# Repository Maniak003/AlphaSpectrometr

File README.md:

<!DOCTYPE html>
<html lang="en" data-color-mode="auto" data-light-theme="light" data-dark-theme="dark">
  <head>
    <meta charset="utf-8">
  </head>
    <body class="logged-in env-production page-responsive page-blob" style="word-wrap: break-word;">
      <p> Alpha spectrometr.<br><b></p>
      
    </body>
</html>

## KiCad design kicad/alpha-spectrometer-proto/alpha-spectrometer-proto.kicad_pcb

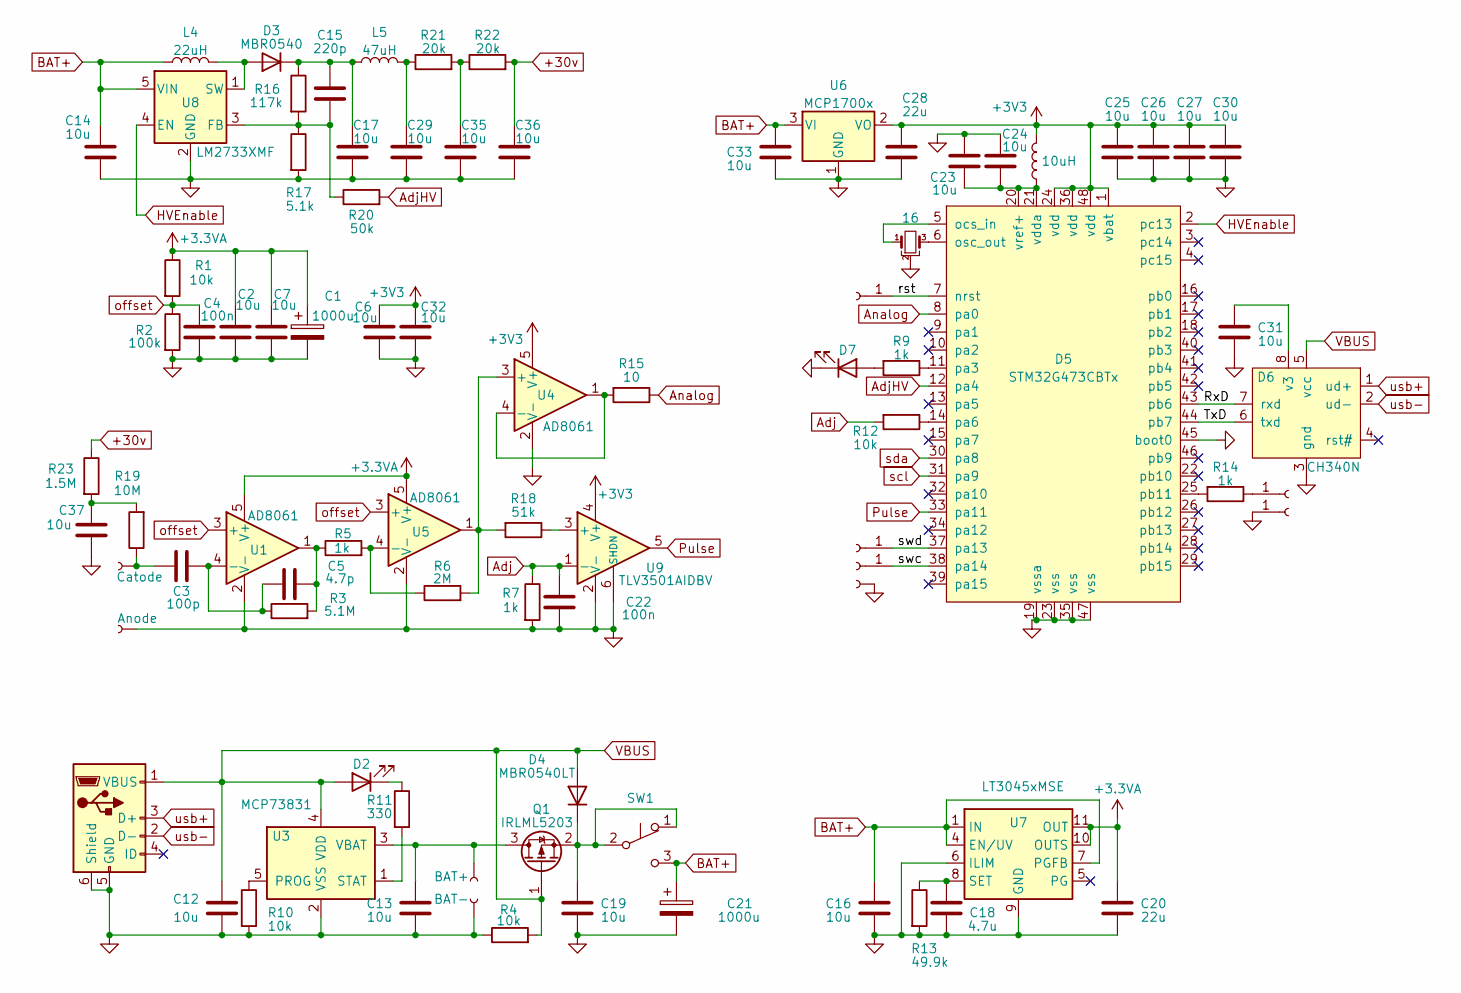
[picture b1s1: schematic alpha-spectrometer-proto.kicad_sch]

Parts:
C1, C21: 1000u; CP_EIA-7132-28_AVX-C
C2, C6, C7, C16, C23, C24, C25, C26, C27, C30, C31, C32, C33, C37: 10u; C_0603_1608Metric
C3: 100p; C_0603_1608Metric
C4, C22: 100n; C_0603_1608Metric
C5: 4.7p; C_0603_1608Metric
C12, C13, C14, C17, C19, C29, C35, C36: 10u; C_0805_2012Metric
C15: 220p; C_0603_1608Metric
C18: 4.7u; C_0603_1608Metric
C20, C28: 22u; C_0603_1608Metric
D2, D7: LED; LED_0603_1608Metric
D3: MBR0540; D_SOD-123
D4: MBR0540LT; D_SOD-123
D5: STM32G473CBTx; LQFP-48_7x7mm_P0.5mm
D6: CH340N; SOP-8_3.9x4.9mm_P1.27mm
J1: USB_B_Micro; USB_Micro-B_Amphenol_10104110_Horizontal
J2, J3, J20, J21, J22: Conn_01x01_Female; conn_mini
J4: BAT+; SMD-CONN
J5: BAT-; SMD-CONN
J13: Anode; Pin_D0.7mm_L6.5mm_W1.8mm_FlatFork
J14: Catode; Pin_D0.7mm_L6.5mm_W1.8mm_FlatFork
J19: Conn; SMD-CONN
L3: 10uH; L_0805_2012Metric
L4: 22uH; L_1206_3216Metric_Pad1.42x1.75mm_HandSolder
L5: 47uH; L_0805_2012Metric
Q1: IRLML5203; SOT-23
R1, R4, R10, R12: 10k; R_0603_1608Metric
R2: 100k; R_0603_1608Metric
R3: 5.1M; R_0603_1608Metric
R5, R7, R9, R14: 1k; R_0603_1608Metric
R6: 2M; R_0603_1608Metric
R11: 330; R_0603_1608Metric
R13: 49.9k; R_0603_1608Metric
R15: 10; R_0603_1608Metric
R16: 117k; R_0603_1608Metric
R17: 5.1k; R_0603_1608Metric
R18: 51k; R_0603_1608Metric
R19: 10M; R_0603_1608Metric
R20: 50k; R_0603_1608Metric
R21, R22: 20k; R_0603_1608Metric
R23: 1.5M; R_0603_1608Metric
SW1: SW_Push_SPDT; MySwithc
U1, U4, U5: AD8061; TSOT-23-5
U3: MCP73831; SOT-23-5
U6: MCP1700x; SOT-23
U7: LT3045xMSE; MSOP-12-1EP_3x4mm_P0.65mm_EP1.65x2.85mm
U8: LM2733XMF; SOT-23-5
U9: TLV3501AIDBV; SOT-23-6
Y1: 16; Resonator_SMD_Murata_CSTxExxV-3Pin_3.0x1.1mm

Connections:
+3.3VA: C1.1, C2.2, C7.2, C20.2, R1.1, U1.5 (V+), U5.5 (V+), U7.10 (OUTS), U7.11 (OUT), U7.12 (OUT)
+3V3: C6.2, C25.2, C26.2, C27.2, C28.2, C30.2, C32.2, D5.1 (vbat), D5.24 (vdd), D5.36 (vdd), D5.48 (vdd), L3.2, U4.5 (V+), U6.2 (VO), U9.4 (V+)
+30v: C36.2, R22.2, R23.1
/RxD: D5.43 (pb6), D6.7 (rxd)
/TxD: D5.44 (pb7), D6.6 (txd)
/rst: D5.7 (nrst), J20.1
/swc: D5.38 (pa14), J22.1
/swd: D5.37 (pa13), J21.1
Adj: C22.2, R7.1, R12.2, U9.1 (-)
AdjHV: D5.12 (pa4), R20.2
Analog: D5.8 (pa0), R15.1
BAT+: C14.2, C16.2, C21.1, C33.2, L4.1, SW1.3 (C), U6.3 (VI), U7.1 (IN), U7.2 (IN), U7.3 (IN), U7.4 (EN/UV), U7.7 (PGFB), U8.5 (VIN)
GND: C1.2, C2.1, C4.1, C6.1, C7.1, C12.1, C13.1, C14.1, C16.1, C17.1, C18.1, C19.1, C20.1, C21.2, C22.1, C23.2, C24.2, C25.1, C26.1, C27.1, C28.1, C29.1, C30.1, C31.1, C32.1, C33.1, C35.1, C36.1, C37.1, D5.19 (vssa), D5.23 (vss), D5.35 (vss), D5.45 (boot0), D5.47 (vss), D6.3 (gnd), D7.1 (K), J1.5 (GND), J1.6 (Shield), J3.1, J5.1, J13.1, J19.1, R2.2, R4.1, R7.2, R10.2, R13.2, R17.2, U1.2 (V-), U3.2 (VSS), U4.2 (V-), U5.2 (V-), U6.1 (GND), U7.6 (ILIM), U7.9 (GND), U7.13 (GND), U8.2 (GND), U9.2 (V-), U9.6 (SHDN), Y1.2
HVEnable: D5.2 (pc13), U8.4 (EN)
unnamed: C3.1, J14.1, R19.1
unnamed: C5.2, R3.2, R5.1, U1.1
unnamed: C29.2, L5.2, R21.1
unnamed: C35.2, R21.2, R22.1
unnamed: C37.2, R19.2, R23.2
unnamed: D2.1 (K), R11.1
unnamed: D3.2 (A), L4.2, U8.1 (SW)
unnamed: C15.2, C17.2, D3.1 (K), L5.1, R16.1
unnamed: C19.2, D4.1 (K), Q1.2 (S), SW1.1 (A), SW1.2 (B)
unnamed: D5.5 (ocs_in), Y1.1
unnamed: D5.6 (osc_out), Y1.3
unnamed: D5.11 (pa3), R9.1
unnamed: D5.14 (pa6), R12.1
unnamed: D5.25 (pb11), R14.2
unnamed: C23.1, C24.1, D5.20 (vref+), D5.21 (vdda), L3.1
unnamed: C31.2, D6.8 (v3)
unnamed: D7.2 (A), R9.2
unnamed: J2.1, R14.1
unnamed: C13.2, J4.1, Q1.3 (D), U3.3 (VBAT)
unnamed: C3.2, C5.1, R3.1, U1.4 (-)
unnamed: R10.1, U3.5 (PROG)
unnamed: R11.2, U3.1 (STAT)
unnamed: R6.2, R18.2, U4.3 (+), U5.1
unnamed: R15.2, U4.1, U4.4 (-)
unnamed: R5.2, R6.1, U5.4 (-)
unnamed: C18.2, R13.1, U7.8 (SET)
unnamed: C15.1, R16.2, R17.1, R20.1, U8.3 (FB)
unnamed: R18.1, U9.3 (+)
Pulse: D5.33 (pa11), U9.5
VBUS: C12.2, D2.2 (A), D4.2 (A), D6.5 (vcc), J1.1 (VBUS), Q1.1 (G), R4.2, U3.4 (VDD)
offset: C4.2, R1.2, R2.1, U1.3 (+), U5.3 (+)
scl: D5.31 (pa9)
sda: D5.30 (pa8)
usb+: D6.1 (ud+), J1.3 (D+)
usb-: D6.2 (ud-), J1.2 (D-)

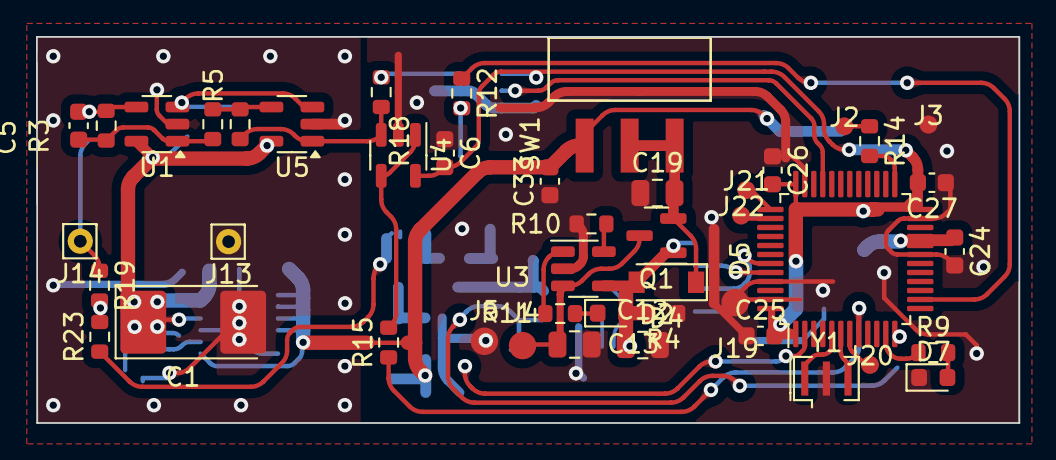
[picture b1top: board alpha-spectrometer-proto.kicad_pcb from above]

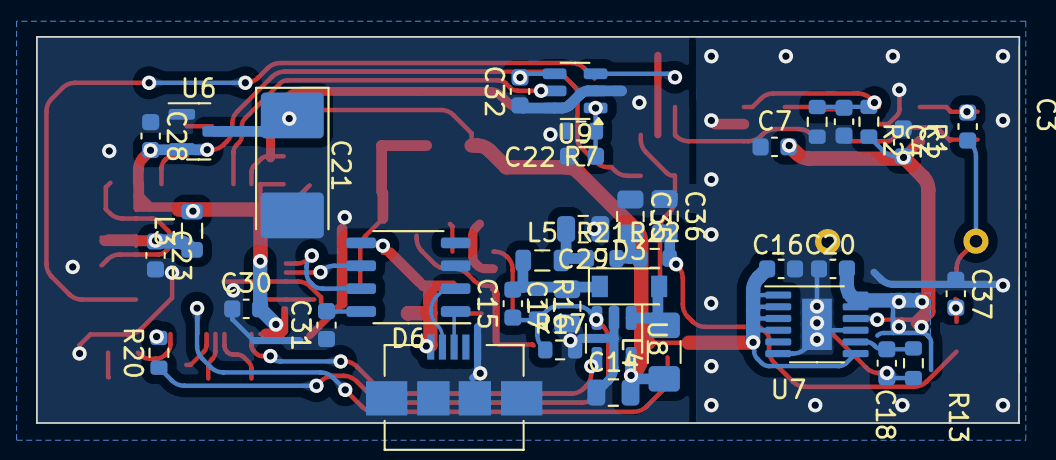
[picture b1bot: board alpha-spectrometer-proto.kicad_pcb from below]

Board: 2 copper layers, 54.6 x 21.5 mm, 85 parts (40 on the bottom side), 47 nets.

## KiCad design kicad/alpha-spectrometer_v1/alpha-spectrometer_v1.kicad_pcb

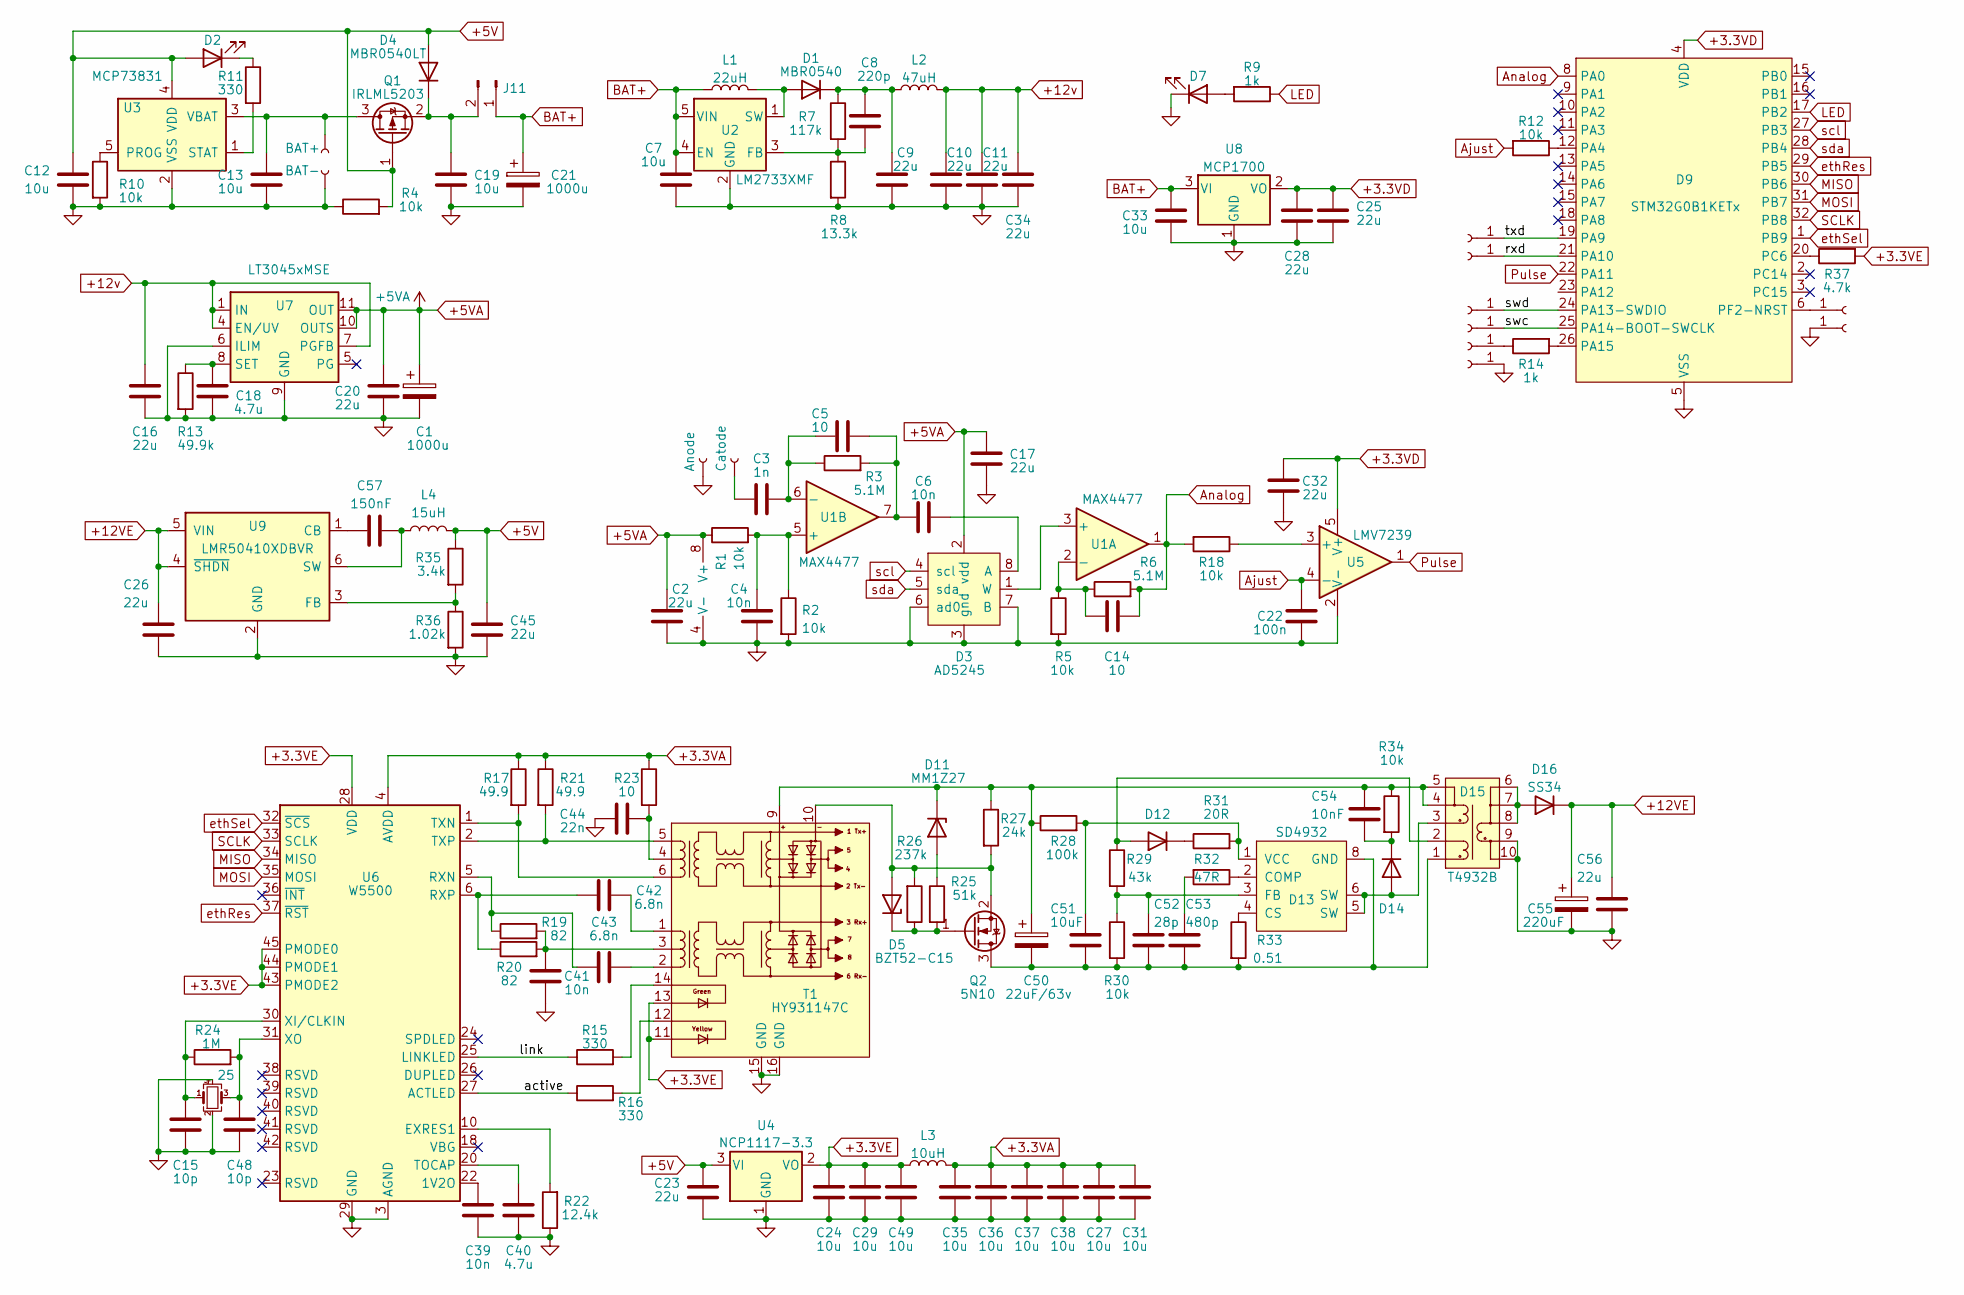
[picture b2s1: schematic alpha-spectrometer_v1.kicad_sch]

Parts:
C1: 1000u; CP_EIA-7132-20_AVX-U
C2, C16, C17, C20, C25, C28, C32: 22u; C_0603_1608Metric
C3: 1n; C_0603_1608Metric
C4, C6, C39, C41: 10n; C_0603_1608Metric
C5, C14: 10; C_0603_1608Metric
C7, C12, C13, C19: 10u; C_0805_2012Metric
C8: 220p; C_0603_1608Metric
C9, C10, C11, C23, C26, C34, C45, C56: 22u; C_0805_2012Metric
C15, C48: 10p; C_0402_1005Metric
C18, C40: 4.7u; C_0603_1608Metric
C21: 1000u; CP_EIA-7343-15_Kemet-W
C22: 100n; C_0603_1608Metric
C24, C27, C29, C31, C33, C35, C36, C37, C38: 10u; C_0603_1608Metric
C42, C43: 6.8n; C_0603_1608Metric
C44: 22n; C_0603_1608Metric
C49: 10u; C_0402_1005Metric
C50: 22uF/63v; CP_Elec_6.3x7.7
C51: 10uF; C_0805_2012Metric
C52: 28p; C_0603_1608Metric
C53: 480p; C_0603_1608Metric
C54: 10nF; C_0603_1608Metric
C55: 220uF; CP_EIA-7343-15_Kemet-W
C57: 150nF; C_0603_1608Metric
D1: MBR0540; D_SOD-123
D2, D7: LED; LED_0603_1608Metric
D3: AD5245; SOT-23-8_Handsoldering
D4: MBR0540LT; D_SOD-123
D5: BZT52-C15; D_SOD-123
D9: STM32G0B1KETx; LQFP-32_7x7mm_P0.8mm
D11: MM1Z27; D_SOD-123
D12, D14: F7; D_SOD-123
D13: SD4932; SOIC-8-N7_3.9x4.9mm_P1.27mm
D15: T4932B; DA2257
D16: SS34; D_SMB
J1, J2, J3, J6, J7, J8, J9, J10: Conn_01x01_Female; conn_mini
J4: BAT+; SMD-CONN
J5: BAT-; SMD-CONN
J11: Conn_01x02_Male; PinHeader_1x02_P2.54mm_Vertical
J13: Anode; Pin_D0.7mm_L6.5mm_W1.8mm_FlatFork
J14: Catode; Pin_D0.7mm_L6.5mm_W1.8mm_FlatFork
L1: 22uH; L_1206_3216Metric_Pad1.42x1.75mm_HandSolder
L2: 47uH; L_0805_2012Metric
L3: 10uH; L_0805_2012Metric
L4: 15uH; L_Abracon_ASPI-0630LR
Q1: IRLML5203; SOT-23
Q2: 5N10; SOT-23
R1, R2, R4, R5, R10, R12, R18, R30, R34: 10k; R_0603_1608Metric
R3, R6: 5.1M; R_0603_1608Metric
R7: 117k; R_0603_1608Metric
R8: 13.3k; R_0603_1608Metric
R9, R14: 1k; R_0603_1608Metric
R11, R15, R16: 330; R_0603_1608Metric
R13: 49.9k; R_0603_1608Metric
R17, R21: 49.9; R_0603_1608Metric
R19, R20: 82; R_0603_1608Metric
R22: 12.4k; R_0603_1608Metric
R23: 10; R_0603_1608Metric
R24: 1M; R_0402_1005Metric
R25: 51k; R_0603_1608Metric
R26: 237k; R_0603_1608Metric
R27: 24k; R_0603_1608Metric
R28: 100k; R_0603_1608Metric
R29: 43k; R_0603_1608Metric
R31: 20R; R_0603_1608Metric
R32: 47R; R_0603_1608Metric
R33: 0.51; R_0603_1608Metric
R35: 3.4k; R_0603_1608Metric
R36: 1.02k; R_0603_1608Metric
R37: 4.7k; R_0603_1608Metric
T1: HY931147C
U1: MAX4477; SSOP-8_2.95x2.8mm_P0.65mm
U2: LM2733XMF; SOT-23-5
U3: MCP73831; SOT-23-5
U4: NCP1117-3.3; SOT-223-3_TabPin2
U5: LMV7239; SOT-23-5
U6: W5500; LQFP-48_7x7mm_P0.5mm
U7: LT3045xMSE; MSOP-12-1EP_3x4mm_P0.65mm_EP1.65x2.85mm
U8: MCP1700; SOT-23
U9: LMR50410XDBVR; SOT-23-6
Y1: 25; Crystal_SMD_TXC_7M-4Pin_3.2x2.5mm

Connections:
+3.3VA: C27.2, C31.2, C35.2, C36.2, C37.2, C38.2, L3.2, R17.1, R21.1, R23.1, U6.4 (AVDD), U6.8 (AVDD), U6.11 (AVDD), U6.15 (AVDD), U6.17 (AVDD), U6.21 (AVDD)
+3.3VD: C25.2, C28.2, C32.2, D9.4 (VDD), U5.5 (V+), U8.2 (VO)
+3.3VE: C24.2, C29.2, C49.2, L3.1, R37.2, T1.11, T1.13, U4.2 (VO), U6.28 (VDD), U6.43 (PMODE2), U6.44 (PMODE1), U6.45 (PMODE0)
+5V: C12.2, C23.2, C45.2, D2.2 (A), D4.2 (A), L4.2, Q1.1 (G), R4.2, R35.1, U3.4 (VDD), U4.3 (VI)
+5VA: C1.1, C2.2, C17.2, C20.2, D3.2 (vdd), R1.1, U1.8 (V+), U7.10 (OUTS), U7.11 (OUT), U7.12 (OUT)
+12VE: C26.1, C55.1, C56.1, D16.1 (K), U9.4 (~SHDN), U9.5 (VIN)
+12v: C10.2, C11.2, C16.2, C34.2, L2.2, U7.1 (IN), U7.2 (IN), U7.3 (IN), U7.4 (EN/UV), U7.7 (PGFB)
/active: R16.1, U6.27 (ACTLED)
/link: R15.1, U6.25 (LINKLED)
/rxd: D9.21 (PA10), J9.1
/swc: D9.25 (PA14-BOOT-SWCLK), J7.1
/swd: D9.24 (PA13-SWDIO), J6.1
/txd: D9.19 (PA9), J1.1
Ajust: C22.2, R12.2, U5.4 (-)
Analog: C14.2, D9.8 (PA0), R6.2, R18.2, U1.1
BAT+: C7.2, C21.1, C33.2, J11.1, L1.1, U2.4 (EN), U2.5 (VIN), U8.3 (VI)
GND: C1.2, C2.1, C4.1, C7.1, C9.1, C10.1, C11.1, C12.1, C13.1, C15.2, C16.1, C17.1, C18.1, C19.1, C20.1, C21.2, C22.1, C23.1, C24.1, C25.1, C26.2, C27.1, C28.1, C29.1, C31.1, C32.1, C33.1, C34.1, C35.1, C36.1, C37.1, C38.1, C39.2, C40.2, C41.1, C44.2, C45.1, C48.2, C49.1, C55.2, C56.2, D3.3 (gnd), D3.6 (ad0), D3.7 (B), D7.1 (K), D9.5 (VSS), D15.9, D15.10, J3.1, J5.1, J10.1, J13.1, R2.2, R4.1, R5.2, R8.2, R10.2, R13.2, R22.1, R36.2, T1.15 (GND), T1.16 (GND), U1.4 (V-), U2.2 (GND), U3.2 (VSS), U4.1 (GND), U5.2 (V-), U6.3 (AGND), U6.9 (AGND), U6.14 (AGND), U6.16 (AGND), U6.19 (AGND), U6.29 (GND), U6.48 (AGND), U7.6 (ILIM), U7.9 (GND), U7.13 (GND), U8.1 (GND), U9.2 (GND), Y1.2, Y1.4
LED: D9.17 (PB2), R9.1
MISO: D9.30 (PB6), U6.34 (MISO)
MOSI: D9.31 (PB7), U6.35 (MOSI)
unnamed: C3.1, J14.1
unnamed: C4.2, R1.2, R2.1, U1.5 (+)
unnamed: C3.2, C5.1, R3.1, U1.6 (-)
unnamed: C5.2, C6.1, R3.2, U1.7
unnamed: C6.2, D3.8 (A)
unnamed: C8.1, R7.2, R8.1, U2.3 (FB)
unnamed: C8.2, C9.2, D1.1 (K), L2.1, R7.1
unnamed: C13.2, J4.1, Q1.3 (D), U3.3 (VBAT)
unnamed: C14.1, R5.1, R6.1, U1.2 (-)
unnamed: C15.1, R24.1, U6.30 (XI/CLKIN), Y1.1
unnamed: C18.2, R13.1, U7.8 (SET)
unnamed: C19.2, D4.1 (K), J11.2, Q1.2 (S)
unnamed: C39.1, U6.22 (1V2O)
unnamed: C40.1, U6.20 (TOCAP)
unnamed: C41.2, R19.2, R20.2, T1.3
unnamed: C42.1, T1.1
unnamed: C42.2, R20.1, U6.6 (RXP)
unnamed: C43.1, T1.2
unnamed: C43.2, R19.1, U6.5 (RXN)
unnamed: C44.1, R23.2, T1.4
unnamed: C48.1, R24.2, U6.31 (XO), Y1.3
unnamed: C50.1, C54.1, D11.1 (K), D15.4, D15.5, R27.1, R28.1, R34.1, T1.9
unnamed: C50.2, C51.2, C52.2, C53.2, D13.8 (GND), D15.1, Q2.3 (D), R30.2, R33.2
unnamed: C51.1, D13.1 (VCC), R28.2, R31.2
unnamed: C52.1, D13.3 (FB), R29.2, R30.1
unnamed: C53.1, R32.2
unnamed: C54.2, D14.1 (K), R34.2
unnamed: C57.1, U9.1 (CB)
unnamed: C57.2, L4.1, U9.6 (SW)
unnamed: D1.2 (A), L1.2, U2.1 (SW)
unnamed: D2.1 (K), R11.1
unnamed: D3.1 (W), U1.3 (+)
unnamed: D5.1 (K), Q2.1 (G), R25.2, R26.1
unnamed: D5.2 (A), Q2.2 (S), R26.2, R27.2, T1.10
unnamed: D7.2 (A), R9.2
unnamed: D9.6 (PF2-NRST), J8.1
unnamed: D9.12 (PA4), R12.1
unnamed: D9.20 (PC6), R37.1
unnamed: D9.26 (PA15), R14.2
unnamed: D11.2 (A), R25.1
unnamed: D12.1 (K), R31.1
unnamed: D12.2 (A), D15.2, R29.1
unnamed: D13.2 (COMP), R32.1
unnamed: D13.4 (CS), R33.1
unnamed: D13.5 (SW), D13.6 (SW), D14.2 (A), D15.3
unnamed: D15.6, D15.7, D15.8, D16.2 (A)
unnamed: J2.1, R14.1
unnamed: R10.1, U3.5 (PROG)
unnamed: R11.2, U3.1 (STAT)
unnamed: R15.2, T1.14
unnamed: R16.2, T1.12
unnamed: R17.2, T1.6, U6.1 (TXN)
unnamed: R18.1, U5.3 (+)
unnamed: R21.2, T1.5, U6.2 (TXP)
unnamed: R22.2, U6.10 (EXRES1)
unnamed: R35.2, R36.1, U9.3 (FB)
Pulse: D9.22 (PA11), U5.1
SCLK: D9.32 (PB8), U6.33 (SCLK)
ethRes: D9.29 (PB5), U6.37 (~RST)
ethSel: D9.1 (PB9), U6.32 (~SCS)
scl: D3.4 (scl), D9.27 (PB3)
sda: D3.5 (sda), D9.28 (PB4)

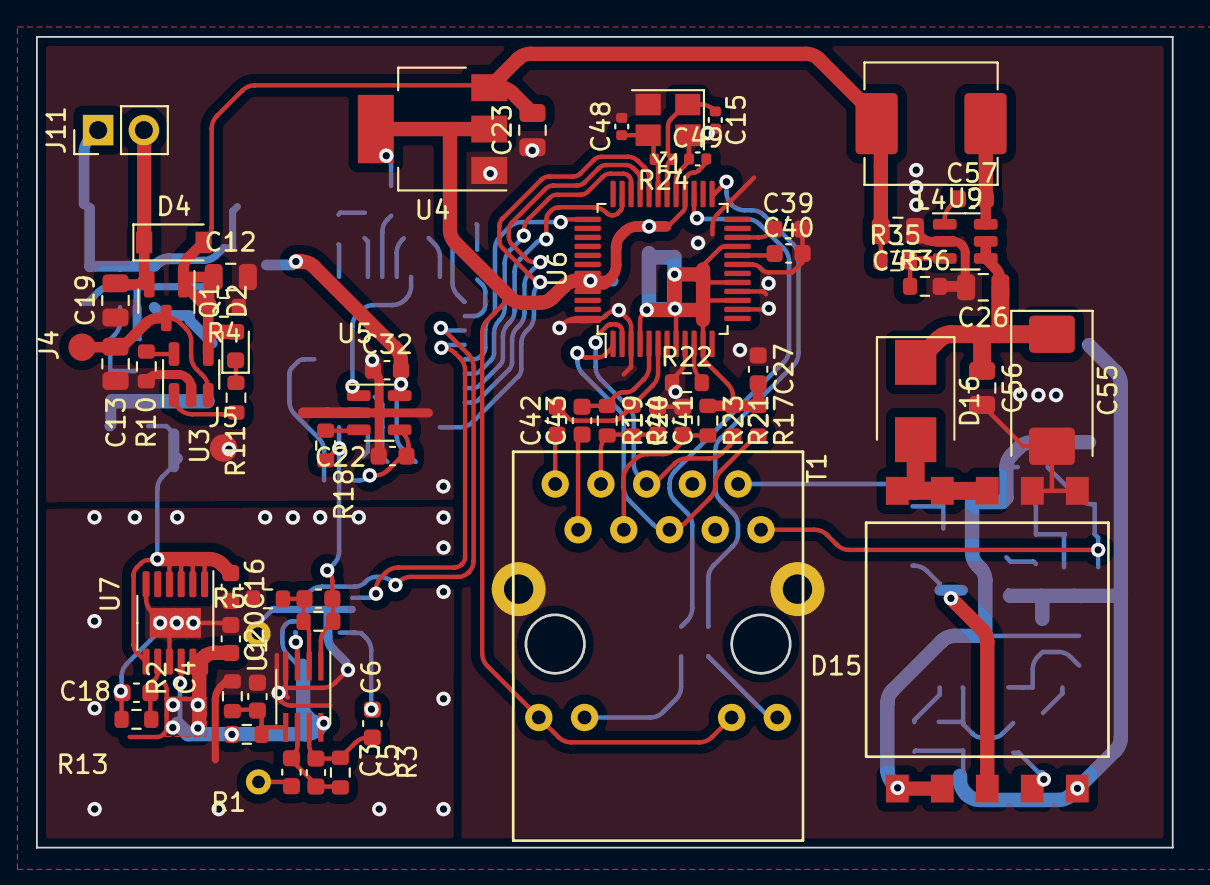
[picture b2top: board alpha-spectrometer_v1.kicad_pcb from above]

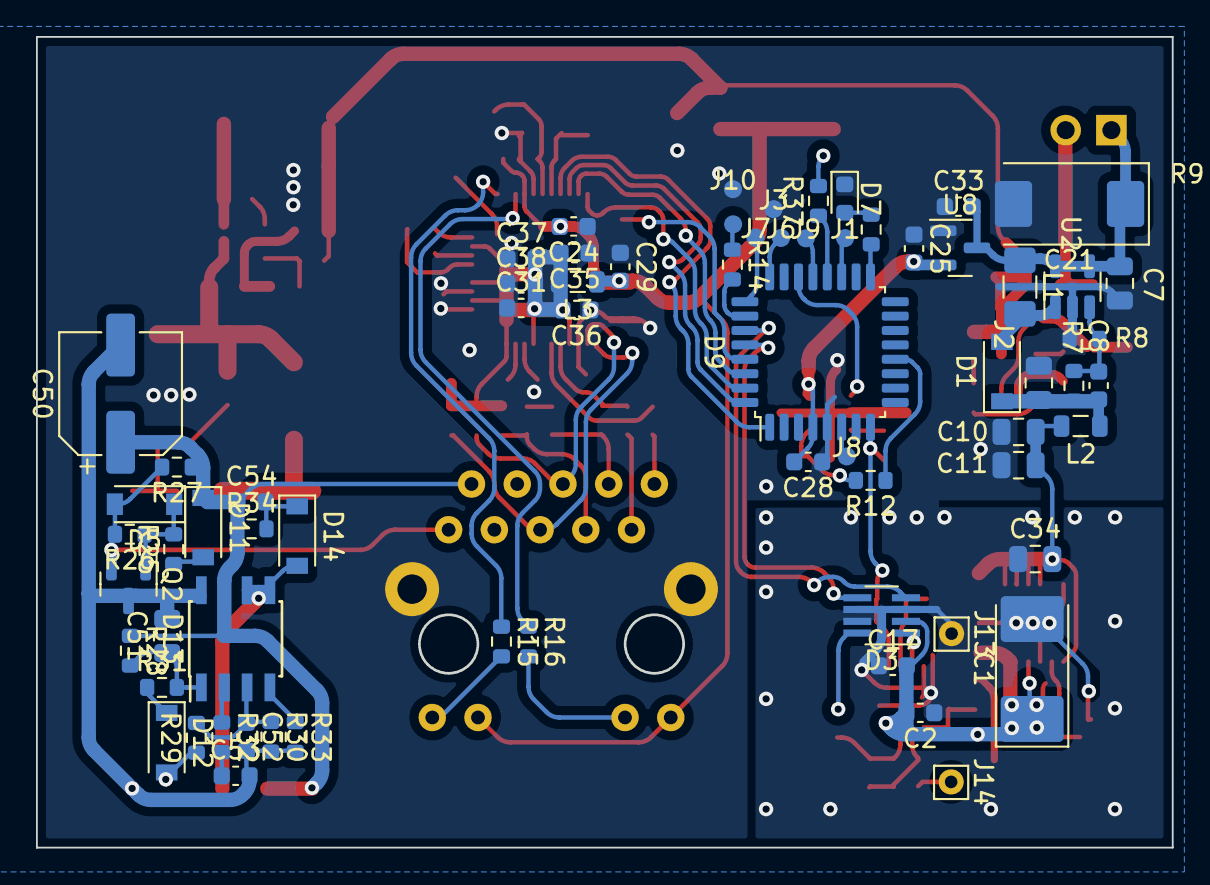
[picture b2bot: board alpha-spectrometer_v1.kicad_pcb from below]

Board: 2 copper layers, 63.1 x 45.0 mm, 134 parts (68 on the bottom side), 82 nets.

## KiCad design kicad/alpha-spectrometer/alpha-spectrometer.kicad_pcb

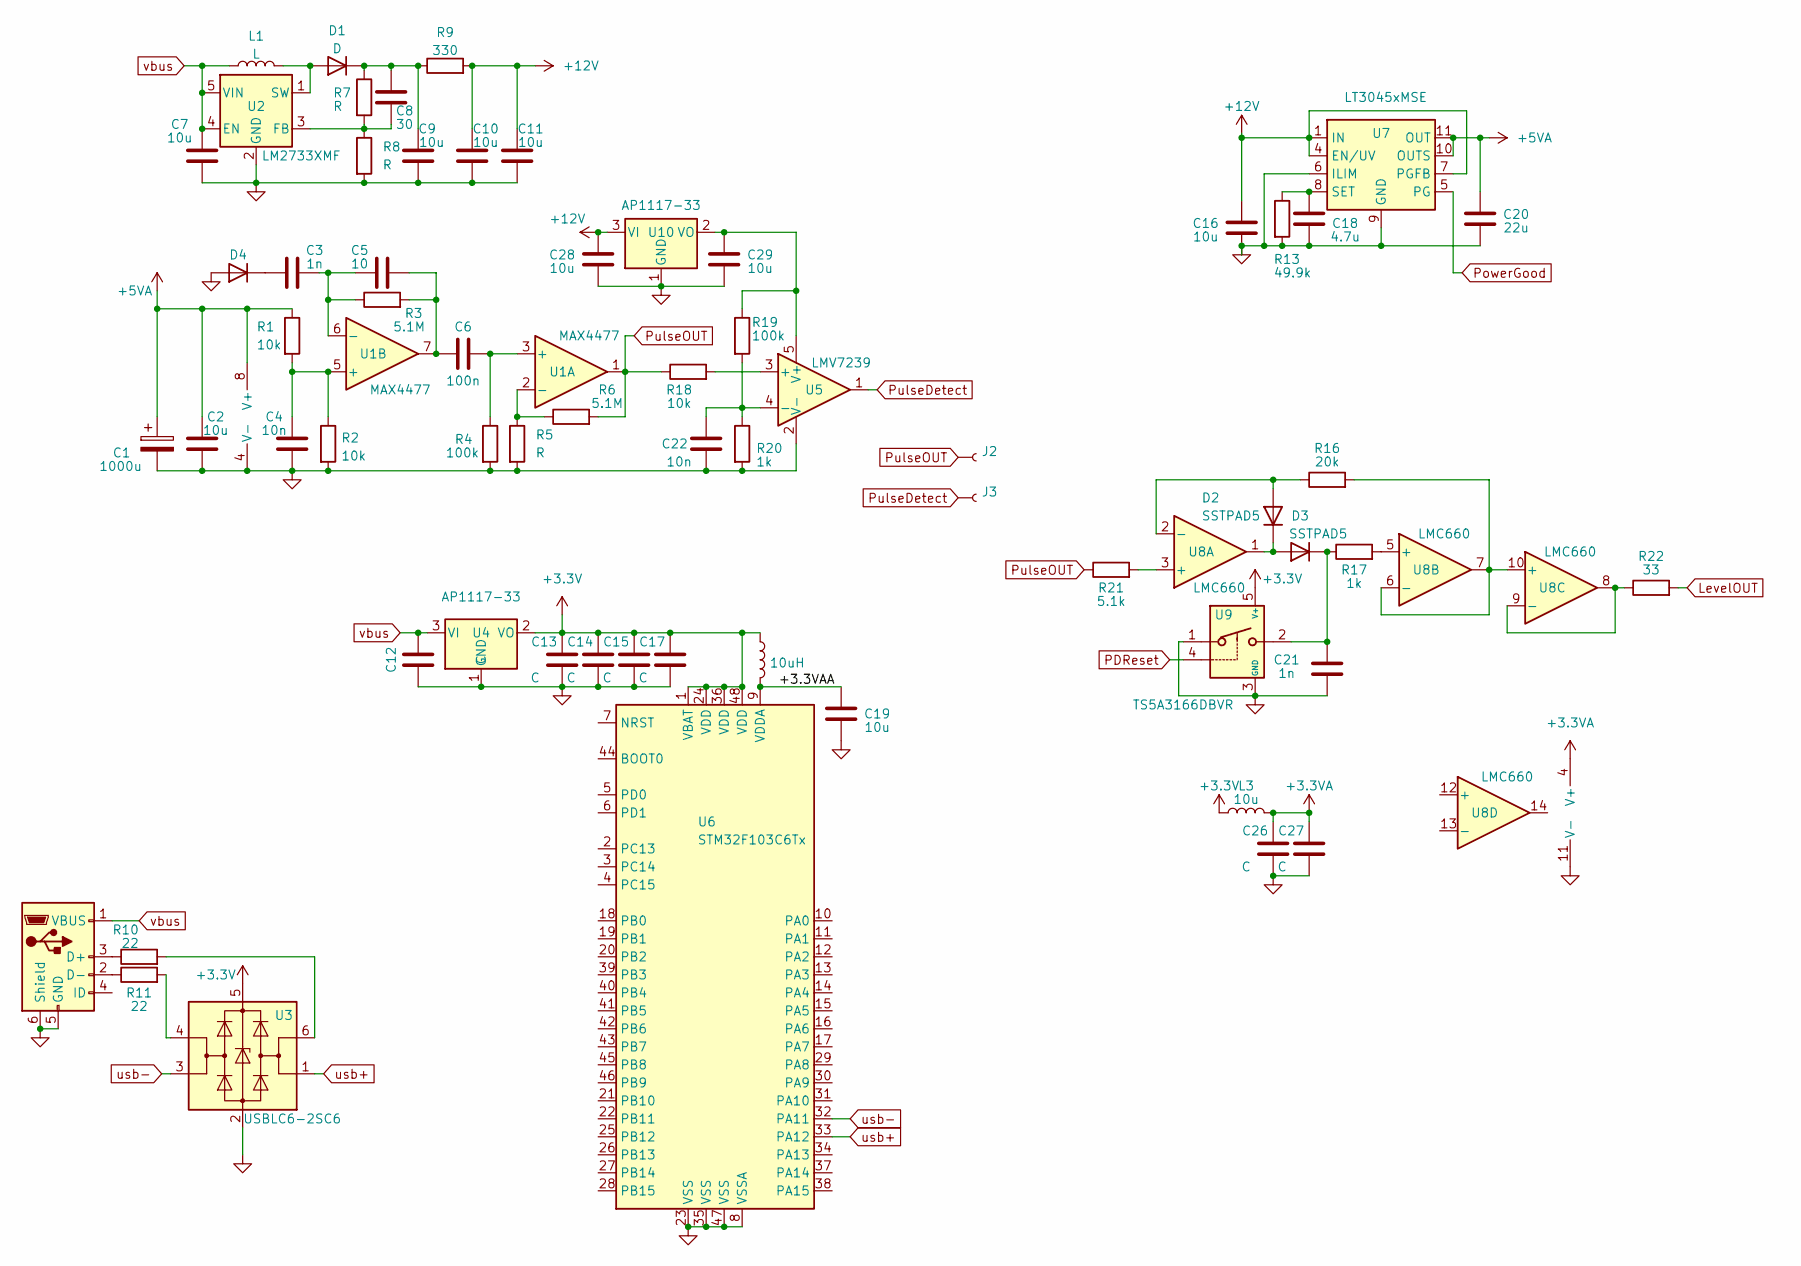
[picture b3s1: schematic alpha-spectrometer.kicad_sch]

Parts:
C1: 1000u; CP_EIA-7132-28_AVX-C
C2, C16, C19, C28, C29: 10u; C_0603_1608Metric
C3, C21: 1n; C_0603_1608Metric
C4, C22: 10n; C_0603_1608Metric
C5: 10; C_0603_1608Metric
C6: 100n; C_0603_1608Metric
C7, C9, C10, C11: 10u; C_0805_2012Metric
C8: 30; C_0603_1608Metric
C12: C; C_0805_2012Metric
C13, C14, C15, C17, C26, C27: C; C_0603_1608Metric
C18: 4.7u; C_0603_1608Metric
C20: 22u; C_0603_1608Metric
D1: D; D_SOD-123
D2, D3: SSTPAD5; D_SOD-123
D4: DIODE; 2DU10
J1: USB_B_Micro; USB_Micro-B_Amphenol_10104110_Horizontal
J2, J3: Conn; SMD-CONN
L1: L; L_1812_4532Metric
L2: 10uH; L_0805_2012Metric
L3: 10u; L_0805_2012Metric
R1, R2, R18: 10k; R_0603_1608Metric
R3, R6: 5.1M; R_0603_1608Metric
R4, R19: 100k; R_0603_1608Metric
R5, R7, R8: R; R_0603_1608Metric
R9: 330; R_0603_1608Metric
R10, R11: 22; R_0603_1608Metric
R13: 49.9k; R_0603_1608Metric
R16: 20k; R_0603_1608Metric
R17, R20: 1k; R_0603_1608Metric
R21: 5.1k; R_0603_1608Metric
R22: 33; R_0603_1608Metric
U1: MAX4477; SSOP-8_2.95x2.8mm_P0.65mm
U2: LM2733XMF; SOT-23-5
U3: USBLC6-2SC6; SOT-23-6
U4, U10: AP1117-33; SOT-223-3_TabPin2
U5: LMV7239; SOT-23-5
U6: STM32F103C6Tx; LQFP-48_7x7mm_P0.5mm
U7: LT3045xMSE; MSOP-12-1EP_3x4mm_P0.65mm_EP1.65x2.85mm
U8: LMC660; SOIC-14_3.9x8.7mm_P1.27mm
U9: TS5A3166DBVR; SOT-23-5

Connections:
+3.3V: C13.2, C14.2, C15.2, C17.2, L2.1, L3.1, U3.5 (VBUS), U4.2 (VO), U6.1 (VBAT), U6.24 (VDD), U6.36 (VDD), U6.48 (VDD), U9.5 (V+)
+3.3VA: C26.2, C27.2, L3.2, U8.4 (V+)
+5VA: C1.1, C2.2, C20.2, R1.1, U1.8 (V+), U7.10 (OUTS), U7.11 (OUT), U7.12 (OUT)
+12V: C10.2, C11.2, C16.2, C28.2, R9.2, U7.1 (IN), U7.2 (IN), U7.3 (IN), U7.4 (EN/UV), U7.7 (PGFB), U10.3 (VI)
/+3.3VAA: C19.2, L2.2, U6.9 (VDDA)
GND: C1.2, C2.1, C4.1, C7.1, C9.1, C10.1, C11.1, C12.1, C13.1, C14.1, C15.1, C16.1, C17.1, C18.1, C19.1, C20.1, C21.1, C22.1, C26.1, C27.1, C28.1, C29.1, D4.1 (A), J1.5 (GND), J1.6 (Shield), R2.2, R4.2, R5.2, R8.2, R13.2, R20.2, U1.4 (V-), U2.2 (GND), U3.2 (GND), U4.1 (GND), U5.2 (V-), U6.8 (VSSA), U6.23 (VSS), U6.35 (VSS), U6.47 (VSS), U7.6 (ILIM), U7.9 (GND), U7.13 (GND), U8.11 (V-), U9.1, U9.3 (GND), U10.1 (GND)
LevelOUT: R22.2
unnamed: C3.1, D4.2 (K)
unnamed: C3.2, C5.1, R3.1, U1.6 (-)
unnamed: C5.2, C6.1, R3.2, U1.7
unnamed: C8.1, R7.2, R8.1, U2.3 (FB)
unnamed: C8.2, C9.2, D1.1 (K), R7.1, R9.1
unnamed: C18.2, R13.1, U7.8 (SET)
unnamed: C21.2, D3.1 (K), R17.1, U9.2
unnamed: C22.2, R19.2, R20.1, U5.4 (-)
unnamed: D1.2 (A), L1.2, U2.1 (SW)
unnamed: D2.1 (K), D3.2 (A), U8.1
unnamed: D2.2 (A), R16.1, U8.2 (-)
unnamed: J1.2 (D-), R11.1
unnamed: J1.3 (D+), R10.1
unnamed: C6.2, R4.1, U1.3 (+)
unnamed: R5.1, R6.1, U1.2 (-)
unnamed: R10.2, U3.6 (I/O1)
unnamed: R11.2, U3.4 (I/O2)
unnamed: R16.2, U8.6 (-), U8.7, U8.10 (+)
unnamed: R17.2, U8.5 (+)
unnamed: R18.2, U5.3 (+)
unnamed: C29.2, R19.1, U5.5 (V+), U10.2 (VO)
unnamed: R21.2, U8.3 (+)
unnamed: R22.1, U8.8, U8.9 (-)
unnamed: C4.2, R1.2, R2.1, U1.5 (+)
PDReset: U9.4
PowerGood: U7.5 (PG)
PulseDetect: J3.1, U5.1
PulseOUT: J2.1, R6.2, R18.1, R21.1, U1.1
usb+: U3.1 (I/O1), U6.33 (PA12)
usb-: U3.3 (I/O2), U6.32 (PA11)
vbus: C7.2, C12.2, J1.1 (VBUS), L1.1, U2.4 (EN), U2.5 (VIN), U4.3 (VI)

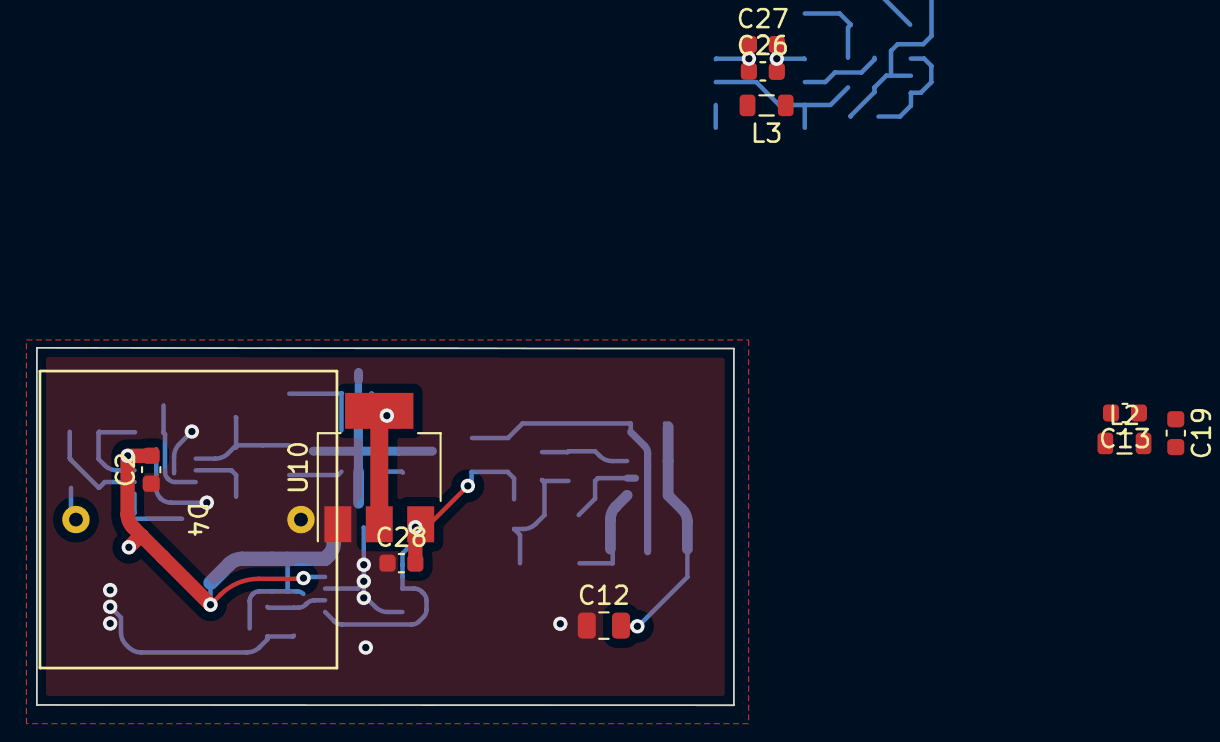
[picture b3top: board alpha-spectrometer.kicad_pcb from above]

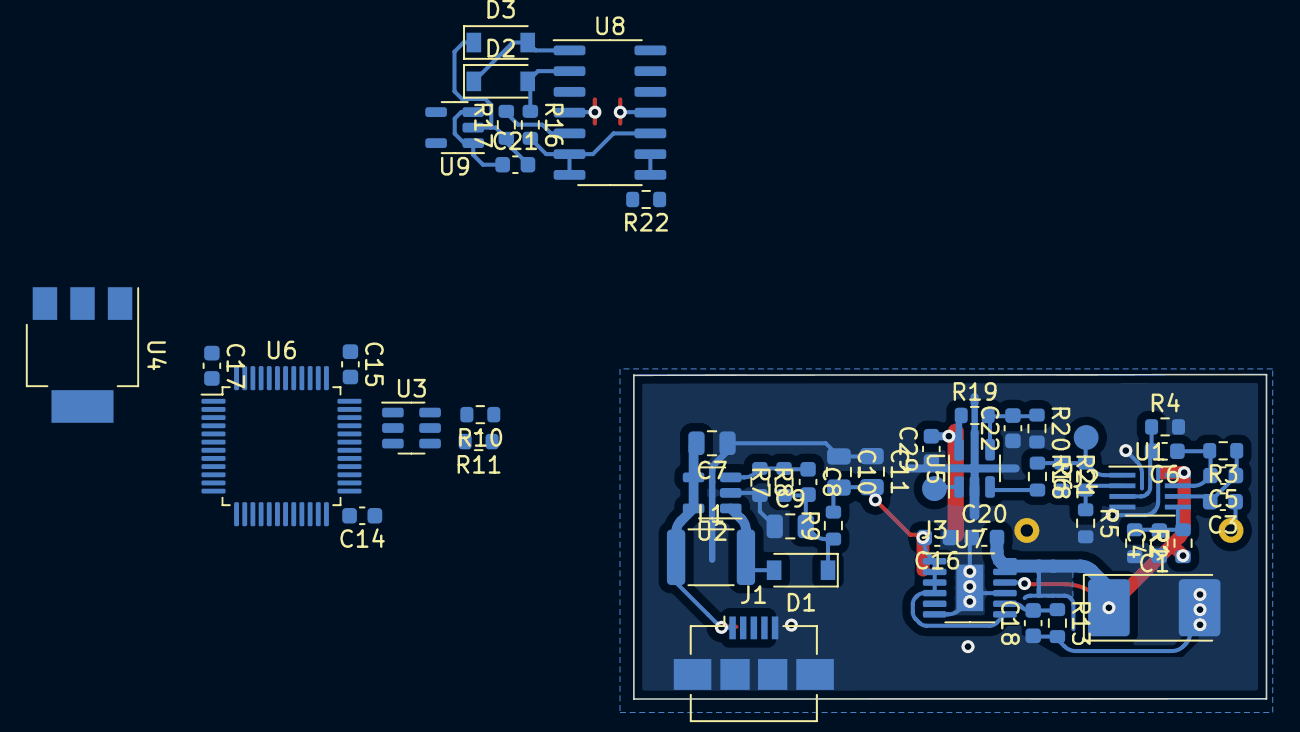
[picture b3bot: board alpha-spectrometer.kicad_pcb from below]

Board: 2 copper layers, 38.7 x 19.9 mm, 65 parts (54 on the bottom side), 35 nets.

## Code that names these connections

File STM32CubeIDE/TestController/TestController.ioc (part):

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Mcu.Name=STM32G473C(B-C-E)Tx
Mcu.Package=LQFP48
Mcu.UserName=STM32G473CBTx
PA0.GPIOParameters=GPIO_Label
PA0.GPIO_Label=AnalogIn
PA0.Mode=IN1-Single-Ended
PA0.Signal=ADC1_IN1
PA11.GPIOParameters=GPIO_Label
PA11.GPIO_Label=ADCsync
PA11.Signal=GPXTI11
PA13.GPIOParameters=GPIO_Label
PA13.GPIO_Label=SWD
PA13.Mode=Serial_Wire
PA13.Signal=SYS_JTMS-SWDIO
PA14.GPIOParameters=GPIO_Label
PA14.GPIO_Label=SWC
PA14.Mode=Serial_Wire
PA14.Signal=SYS_JTCK-SWCLK
PA3.GPIOParameters=GPIO_Label
PA3.GPIO_Label=LED
PA3.Signal=GPIO_Output
PA4.GPIOParameters=GPIO_Label
PA4.GPIO_Label=AdjHV
PA4.Signal=COMP_DAC11_group
PA6.GPIOParameters=GPIO_Label
PA6.GPIO_Label=Comp_level
PA6.Signal=COMP_DAC21_group
PA8.GPIOParameters=GPIO_Pu
PA8.GPIO_Pu=GPIO_PULLUP
PA8.Mode=I2C
PA8.Signal=I2C2_SDA
PA9.GPIOParameters=GPIO_Pu
PA9.GPIO_Pu=GPIO_PULLUP
PA9.Mode=I2C
PA9.Signal=I2C2_SCL
PB11.GPIOParameters=GPIO_Label
PB11.GPIO_Label=PULSE_CLIBRATE
PB11.Signal=S_TIM2_CH4
PB6.GPIOParameters=GPIO_Label
PB6.GPIO_Label=TX
PB6.Mode=Asynchronous
PB6.Signal=USART1_TX
PB7.GPIOParameters=GPIO_Label
PB7.GPIO_Label=RX
PB7.Mode=Asynchronous
PB7.Signal=USART1_RX
PF0-OSC_IN.Mode=HSE-External-Oscillator
PF0-OSC_IN.Signal=RCC_OSC_IN
PF1-OSC_OUT.Mode=HSE-External-Oscillator
PF1-OSC_OUT.Signal=RCC_OSC_OUT
RCC.HSE_VALUE=16000000
RCC.SYSCLKFreq_VALUE=170000000
RCC.SYSCLKSource=RCC_SYSCLKSOURCE_PLLCLK
board=custom

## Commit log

2024-11-04 новый файл: Documents/AM-1.png новый файл: Documents/AM-D1.png новый файл: Documents/AM-D2.png новый файл: Documents/AM-D3.png новый файл: Documents/AS.png новый файл: "Documents/\320\224\320\265\321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
2024-11-05 новый файл: Documents/Rn-D1.png
2024-11-05 изменено: GNUPlot/alpha-4.dat изменено: GNUPlot/mainChart-1.gp
2024-11-05 удалено: kicad/alpha-spectrometer-proto/alpha-spectrometer-proto-backups/alpha-spectrometer-proto-2024-11-04_113452.zip изменено: kicad/alpha-spectrometer-proto/alpha-spectrometer-proto.kicad_pcb изм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
2024-11-06 новый файл: Documents/Rn-D1-2.png новый файл: Documents/Rn-D1-3.png изменено: GNUPlot/alpha-4.dat изменено: GNUPlot/mainChart-1.gp
2024-11-08 изменено: STM32CubeIDE/TestController/.settings/language.settings.xml удалено: kicad/alpha-spectrometer-proto/alpha-spectrometer-proto-backups/alpha-spectrometer-proto-2024-10-29_184757.zip новый фай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
2024-11-08 новый файл: Documents/Rn-D1-4.png изменено: GNUPlot/alpha-4.dat изменено: GNUPlot/mainChart-1.gp
2024-11-13 изменено: GNUPlot/mainChart-1.gp удалено: kicad/alpha-spectrometer-proto/alpha-spectrometer-proto-backups/alpha-spectrometer-proto-2024-10-29_185625.zip удалено: kicad/alpha-spectrometer-proto/alpha-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
2024-11-17 удалено: Documents/mr107+-1.png удалено: Documents/mr107+-10.png удалено: Documents/mr107+-11.png удалено: Documents/mr107+-12.png удалено: Documents/mr107+-13.png удалено: Documents/mr107+-14.png уд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
2024-11-26 новый файл: Documents/AM-D1-10112024-12_5.png новый файл: Documents/AM-D1-10112024-247.png новый файл: Documents/AM-D1-10112024-247_5-10M.png новый файл: Documents/AM-D1-10112024-24_5-10M.png новый ф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
2025-07-05 изменено: STM32CubeIDE/TestController/Debug/TestController.list изменено: STM32CubeIDE/TestController/Debug/makefile удалено: kicad/alpha-spectrometer-proto/alpha-spectrometer-proto-backups/alpha-spe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
2025-07-05 изменено: STM32CubeIDE/TestController/.mxproject изменено: STM32CubeIDE/TestController/.settings/language.settings.xml изменено: STM32CubeIDE/TestController/Core/Inc/main.h изменено: STM32CubeIDE/Tes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
2025-07-06 изменено: STM32CubeIDE/TestController/.mxproject изменено: STM32CubeIDE/TestController/.settings/language.settings.xml изменено: STM32CubeIDE/TestController/Core/Src/main.c изменено: STM32CubeIDE/Tes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
